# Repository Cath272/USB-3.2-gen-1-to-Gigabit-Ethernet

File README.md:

# USB 3.2 gen 1 to Gigabit Ethernet
 Gigabit Ethenet to USB C using VL162 and RTL8153

 ## VL162

  - 4:2 10Gbps USB Type-C Data Switch

  - Low power consumption with 6mW active at device mode

 ## RTL8153 

  - Integrated 10/100/1000M transceiver

  - Supports USB 3.0, 2.0, and 1.1

 ###  Built-in Voltage Regulators

- 5.0V to 3.3V LDO

- 3.3V to 1.2V Switching regulator

 ## TLV70233DBVR

 - 5V to 3.3V LDO for spi flash and leds

 ## W25Q16BVSSIG

 - 16Mbit SPI Flash  

 ## HR911130A
 - RJ45 Port with integrated magnetics 
 - 1000 Base-T Magnetics 

## PCB 
This board uses a 4 layer stackup with a  1.6mm thickness:

- POWER/SIGNAL

- GND
  
- GND
  
- POWER/SIGNAL

High Speed diferential lines need a refrence ground plane so internal planes are ground referance planes for the High speed USB lines

### Schematic:

## PCB Screenshots

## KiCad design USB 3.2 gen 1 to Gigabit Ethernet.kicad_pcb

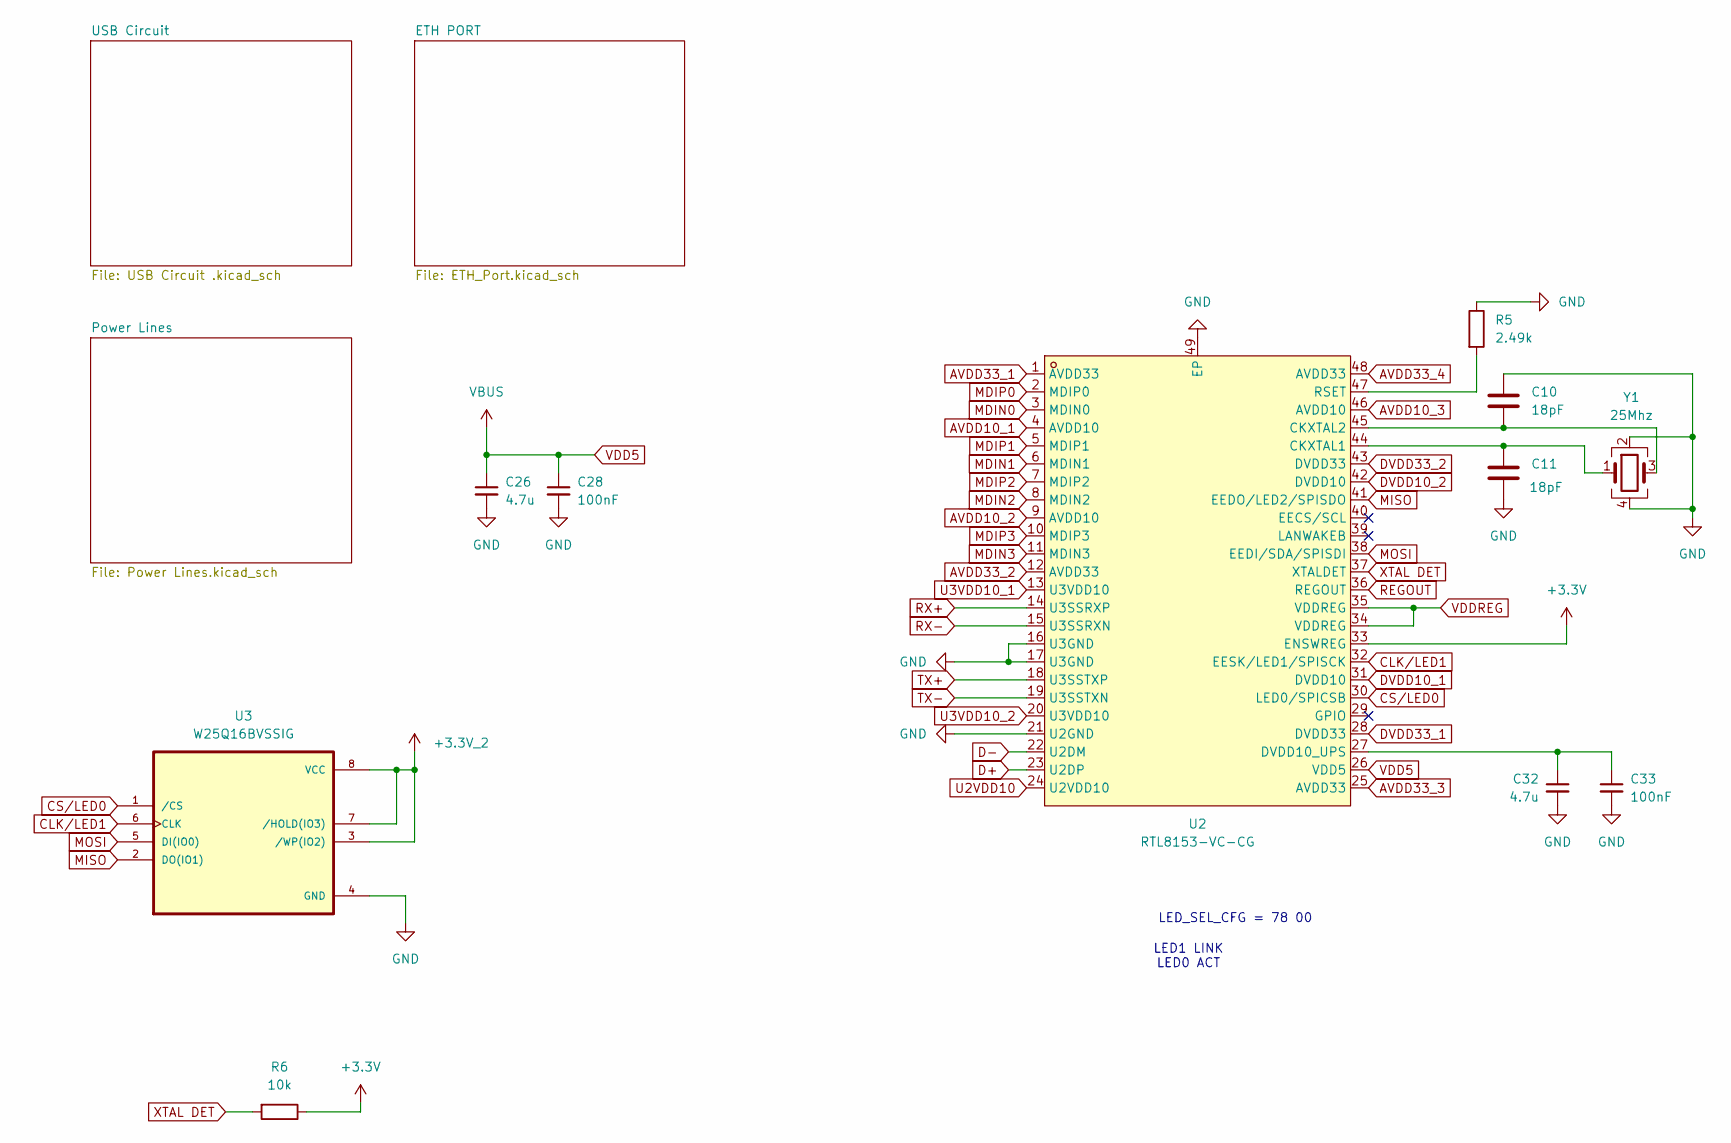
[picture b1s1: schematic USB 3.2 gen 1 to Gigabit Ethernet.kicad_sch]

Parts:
C10, C11: 18pF; C_0402_1005Metric
C26, C32: 4.7u; C_0805_2012Metric
C28, C33: 100nF; C_0402_1005Metric
R5: 2.49k; R_0402_1005Metric
R6: 10k; R_0402_1005Metric
U2: RTL8153-VC-CG; QFN-48_L6.0-W6.0-P0.40-TL-EP4.4; LCSC Part C2764167
U3: W25Q16BVSSIG; SOIC-8_L5.3-W5.3-P1.27-LS8.0-BL; PARTREV F
Y1: 25Mhz; Crystal_SMD_3225-4Pin_3.2x2.5mm

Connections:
+3.3V_2: U3.3 (/WP(IO2)), U3.7 (/HOLD(IO3)), U3.8 (VCC); also elsewhere on the board
AVDD10_1: U2.4 (AVDD10), U2.9 (AVDD10), U2.13 (U3VDD10), U2.20 (U3VDD10), U2.24 (U2VDD10), U2.31 (DVDD10), U2.42 (DVDD10), U2.46 (AVDD10); also elsewhere on the board
AVDD33_1: R6.1, U2.1 (AVDD33), U2.12 (AVDD33), U2.25 (AVDD33), U2.28 (DVDD33), U2.33 (ENSWREG), U2.34 (VDDREG), U2.35 (VDDREG), U2.43 (DVDD33), U2.48 (AVDD33); also elsewhere on the board
CLK/LED1: U2.32 (EESK/LED1/SPISCK), U3.6 (CLK); also elsewhere on the board
CS/LED0: U2.30 (LED0/SPICSB), U3.1 (/CS); also elsewhere on the board
D+: U2.23 (U2DP); also elsewhere on the board
D-: U2.22 (U2DM); also elsewhere on the board
GND: C10.1, C11.2, C26.2, C28.2, C32.2, C33.2, R5.1, U2.16 (U3GND), U2.17 (U3GND), U2.21 (U2GND), U2.49 (EP), U3.4 (GND), Y1.2, Y1.4; also elsewhere on the board
MDIN0: U2.3 (MDIN0); also elsewhere on the board
MDIN1: U2.6 (MDIN1); also elsewhere on the board
MDIN2: U2.8 (MDIN2); also elsewhere on the board
MDIN3: U2.11 (MDIN3); also elsewhere on the board
MDIP0: U2.2 (MDIP0); also elsewhere on the board
MDIP1: U2.5 (MDIP1); also elsewhere on the board
MDIP2: U2.7 (MDIP2); also elsewhere on the board
MDIP3: U2.10 (MDIP3); also elsewhere on the board
MISO: U2.41 (EEDO/LED2/SPISDO), U3.2 (DO(IO1))
MOSI: U2.38 (EEDI/SDA/SPISDI), U3.5 (DI(IO0))
unnamed: C11.1, U2.44 (CKXTAL1), Y1.1
unnamed: C10.2, U2.45 (CKXTAL2), Y1.3
unnamed: C32.1, C33.1, U2.27 (DVDD10_UPS)
unnamed: R5.2, U2.47 (RSET)
REGOUT: U2.36 (REGOUT); also elsewhere on the board
RX+: U2.14 (U3SSRXP); also elsewhere on the board
RX-: U2.15 (U3SSRXN); also elsewhere on the board
TX+: U2.18 (U3SSTXP); also elsewhere on the board
TX-: U2.19 (U3SSTXN); also elsewhere on the board
VDD5: C26.1, C28.1, U2.26 (VDD5); also elsewhere on the board
XTAL DET: R6.2, U2.37 (XTALDET)

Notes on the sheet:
LED_SEL_CFG = 78 00
LED1 LINK LED0 ACT

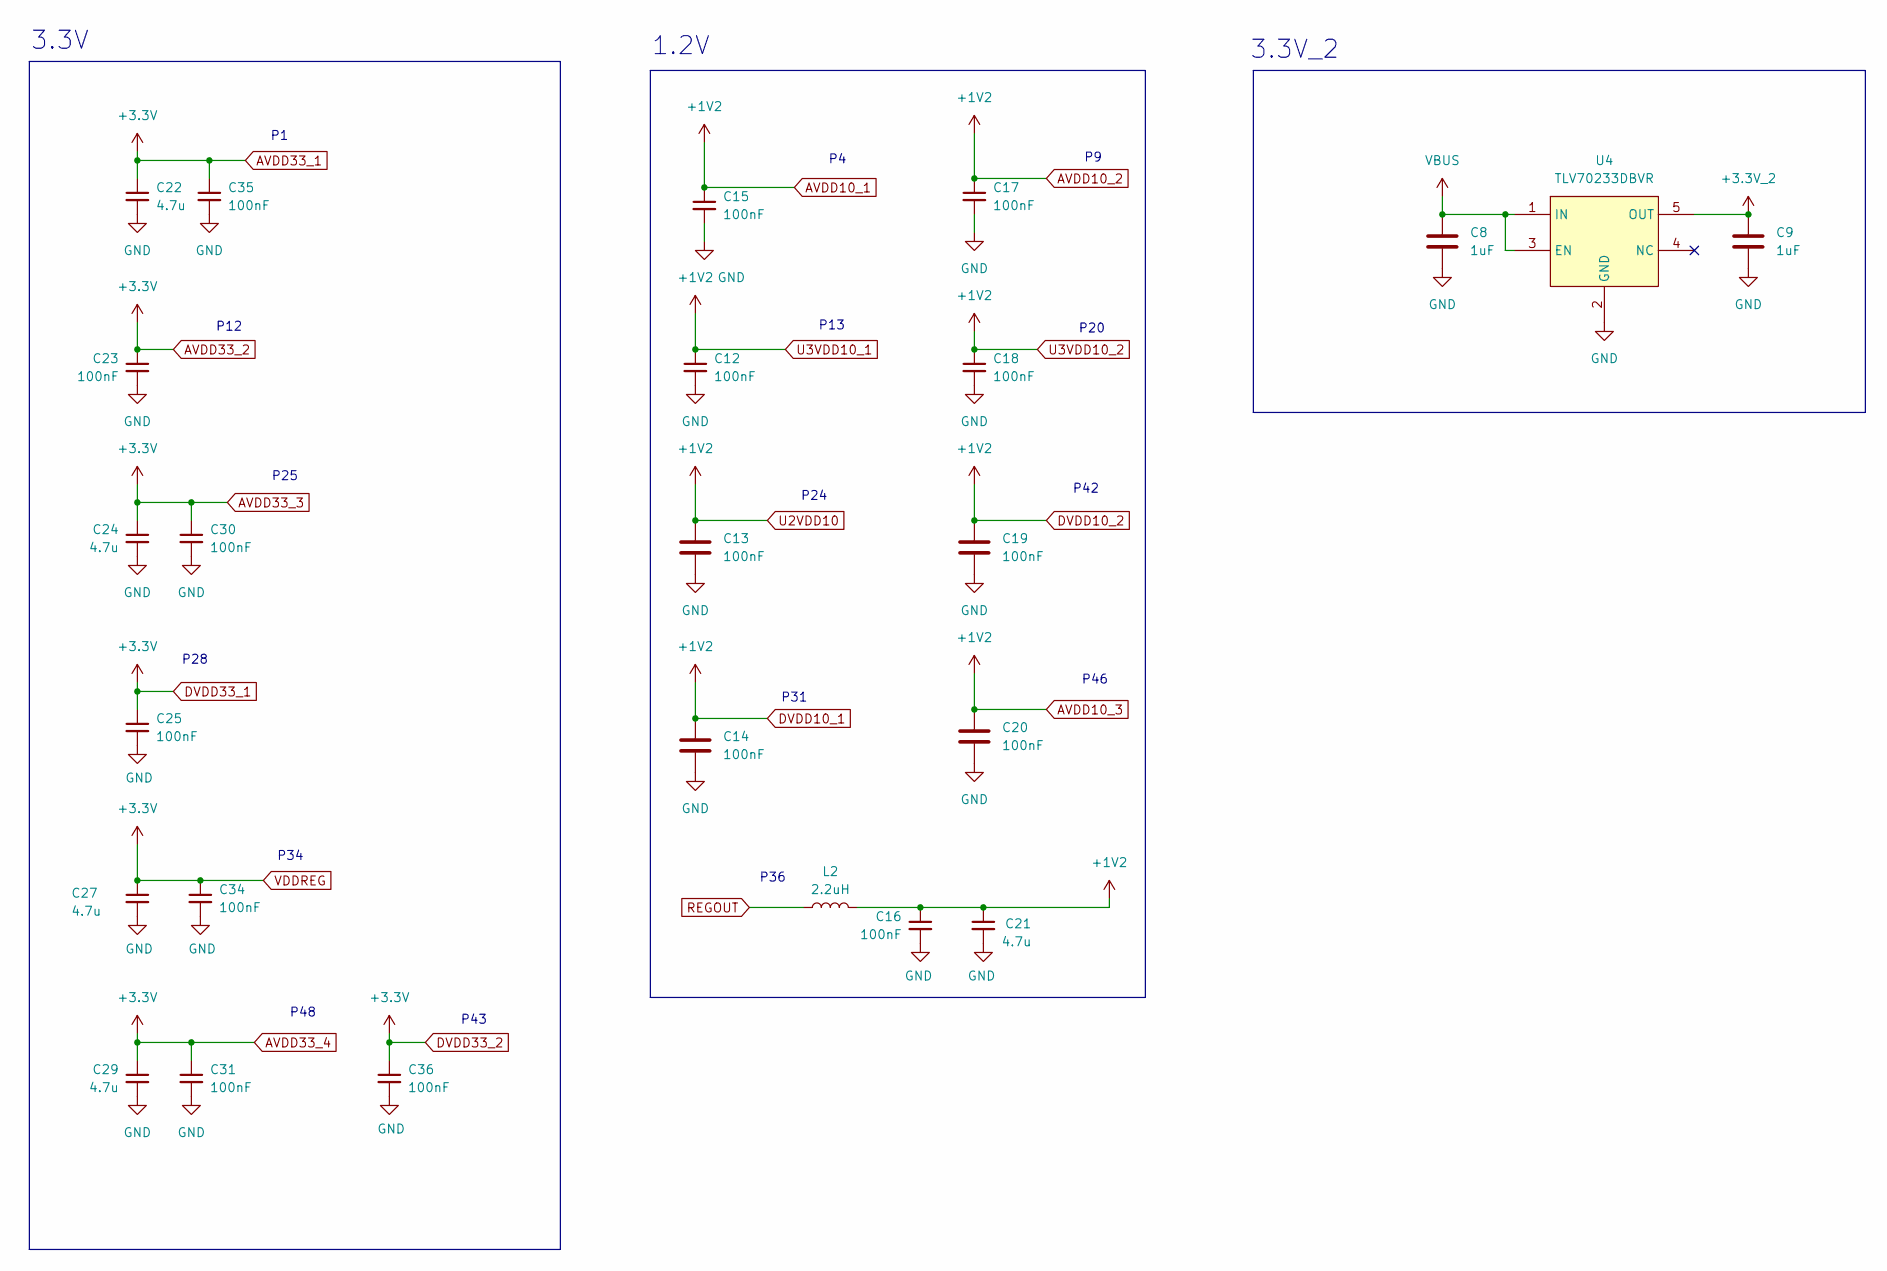
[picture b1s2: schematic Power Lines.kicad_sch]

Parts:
C8, C9: 1uF; C_0603_1608Metric
C12, C13, C14, C15, C16, C17, C18, C19, C20, C23, C25, C30, C31, C34, C35, C36: 100nF; C_0402_1005Metric
C21, C22, C24, C27, C29: 4.7u; C_0805_2012Metric
L2: 2.2uH; L_Cenker_CKCS5040
U4: TLV70233DBVR; SOT-23-5_L3.0-W1.7-P0.95-LS2.8-BR; LCSC Part C26833

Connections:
+3.3V_2: C9.1, U4.5 (OUT); also elsewhere on the board
AVDD10_1: C12.1, C13.1, C14.1, C15.1, C16.1, C17.1, C18.1, C19.1, C20.1, C21.1, L2.2; also elsewhere on the board
AVDD33_1: C22.1, C23.1, C24.1, C25.1, C27.1, C29.1, C30.1, C31.1, C34.1, C35.1, C36.1; also elsewhere on the board
GND: C8.2, C9.2, C12.2, C13.2, C14.2, C15.2, C16.2, C17.2, C18.2, C19.2, C20.2, C21.2, C22.2, C23.2, C24.2, C25.2, C27.2, C29.2, C30.2, C31.2, C34.2, C35.2, C36.2, U4.2 (GND); also elsewhere on the board
REGOUT: L2.1; also elsewhere on the board
VDD5: C8.1, U4.1 (IN), U4.3 (EN); also elsewhere on the board

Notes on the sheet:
P36
P42
P20
P28
P31
3.3V
P25
P24
P12
P13
1.2V
P48
3.3V_2
P46
P43
P34

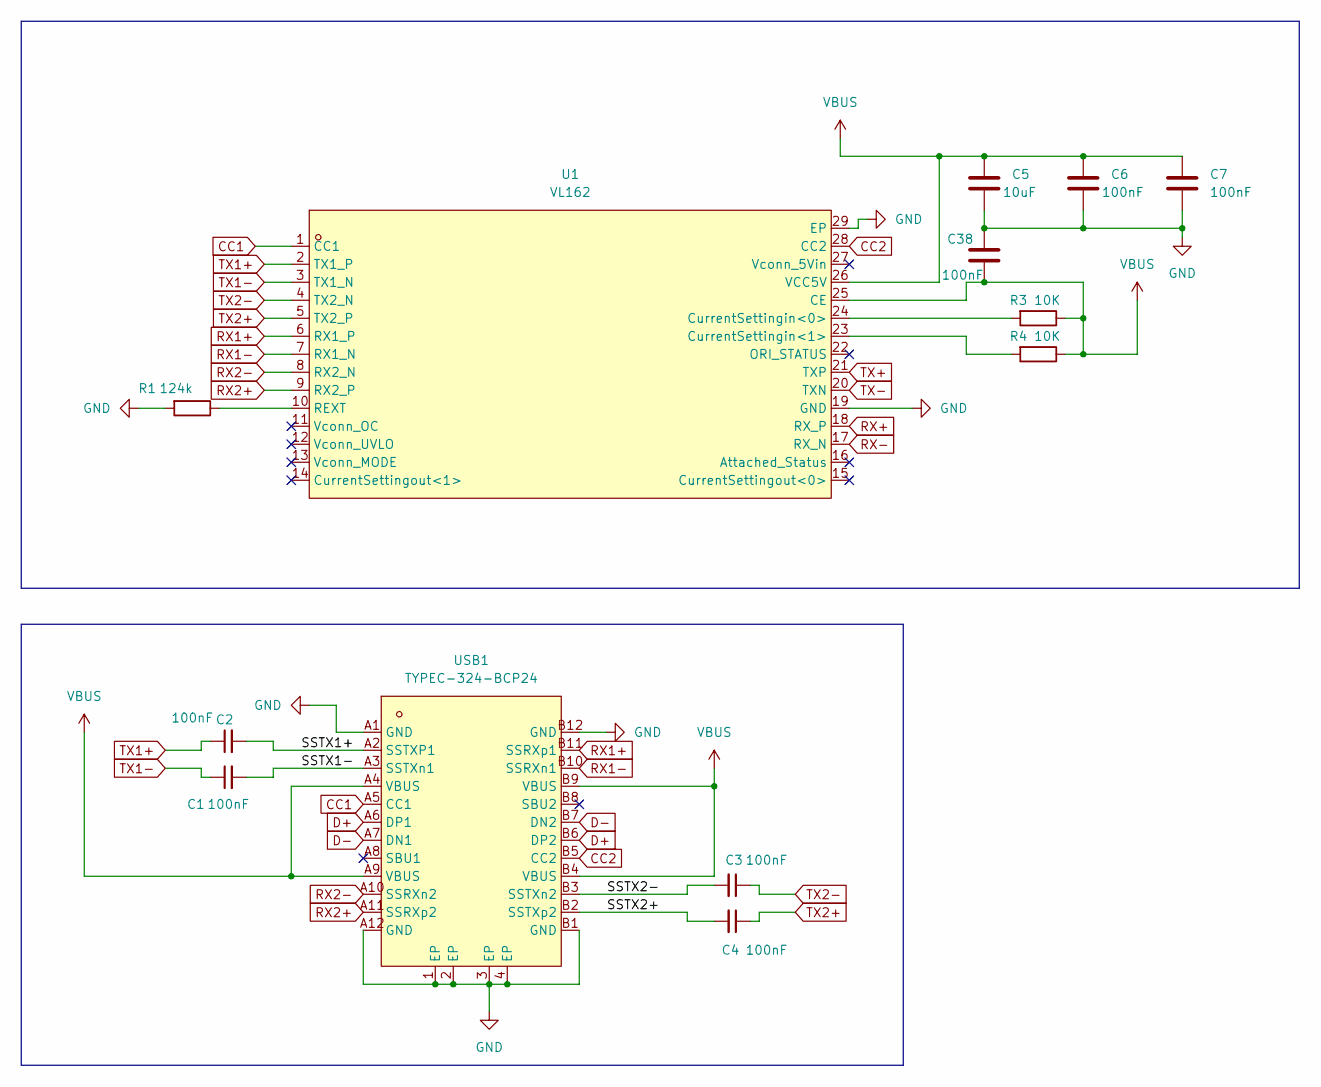
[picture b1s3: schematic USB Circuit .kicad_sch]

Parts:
C1, C2, C3, C4, C6, C7, C38: 100nF; C_0402_1005Metric
C5: 10uF; C_0805_2012Metric
R1: 124k; R_0402_1005Metric
R3, R4: 10K; R_0402_1005Metric
U1: VL162; MQFN-28_L4.5-W3.5-P0.40-BL-EP; LCSC Part C19270896
USB1: TYPEC-324-BCP24; USB-C-SMD_TYPEC-324-BCP24; LCSC Part C2835314

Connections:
/USB Circuit /SSTX1+: C2.2, USB1.A2 (SSTXP1)
/USB Circuit /SSTX1-: C1.2, USB1.A3 (SSTXn1)
/USB Circuit /SSTX2+: C4.2, USB1.B2 (SSTXp2)
/USB Circuit /SSTX2-: C3.2, USB1.B3 (SSTXn2)
CC1: U1.1 (CC1), USB1.A5 (CC1)
CC2: U1.28 (CC2), USB1.B5 (CC2)
D+: USB1.A6 (DP1), USB1.B6 (DP2); also elsewhere on the board
D-: USB1.A7 (DN1), USB1.B7 (DN2); also elsewhere on the board
GND: C5.2, C6.2, C7.2, C38.1, R1.2, U1.19 (GND), U1.29 (EP), USB1.1 (EP), USB1.2 (EP), USB1.3 (EP), USB1.4 (EP), USB1.A1 (GND), USB1.A12 (GND), USB1.B1 (GND), USB1.B12 (GND); also elsewhere on the board
unnamed: R3.2, U1.24 (CurrentSettingin<0>)
unnamed: R4.2, U1.23 (CurrentSettingin<1>)
unnamed: R1.1, U1.10 (REXT)
RX1+: U1.6 (RX1_P), USB1.B11 (SSRXp1)
RX1-: U1.7 (RX1_N), USB1.B10 (SSRXn1)
RX2+: U1.9 (RX2_P), USB1.A11 (SSRXp2)
RX2-: U1.8 (RX2_N), USB1.A10 (SSRXn2)
RX+: U1.18 (RX_P); also elsewhere on the board
RX-: U1.17 (RX_N); also elsewhere on the board
TX1+: C2.1, U1.2 (TX1_P)
TX1-: C1.1, U1.3 (TX1_N)
TX2+: C4.1, U1.5 (TX2_P)
TX2-: C3.1, U1.4 (TX2_N)
TX+: U1.21 (TXP); also elsewhere on the board
TX-: U1.20 (TXN); also elsewhere on the board
VDD5: C5.1, C6.1, C7.1, C38.2, R3.1, R4.1, U1.25 (CE), U1.26 (VCC5V), USB1.A4 (VBUS), USB1.A9 (VBUS), USB1.B4 (VBUS), USB1.B9 (VBUS); also elsewhere on the board

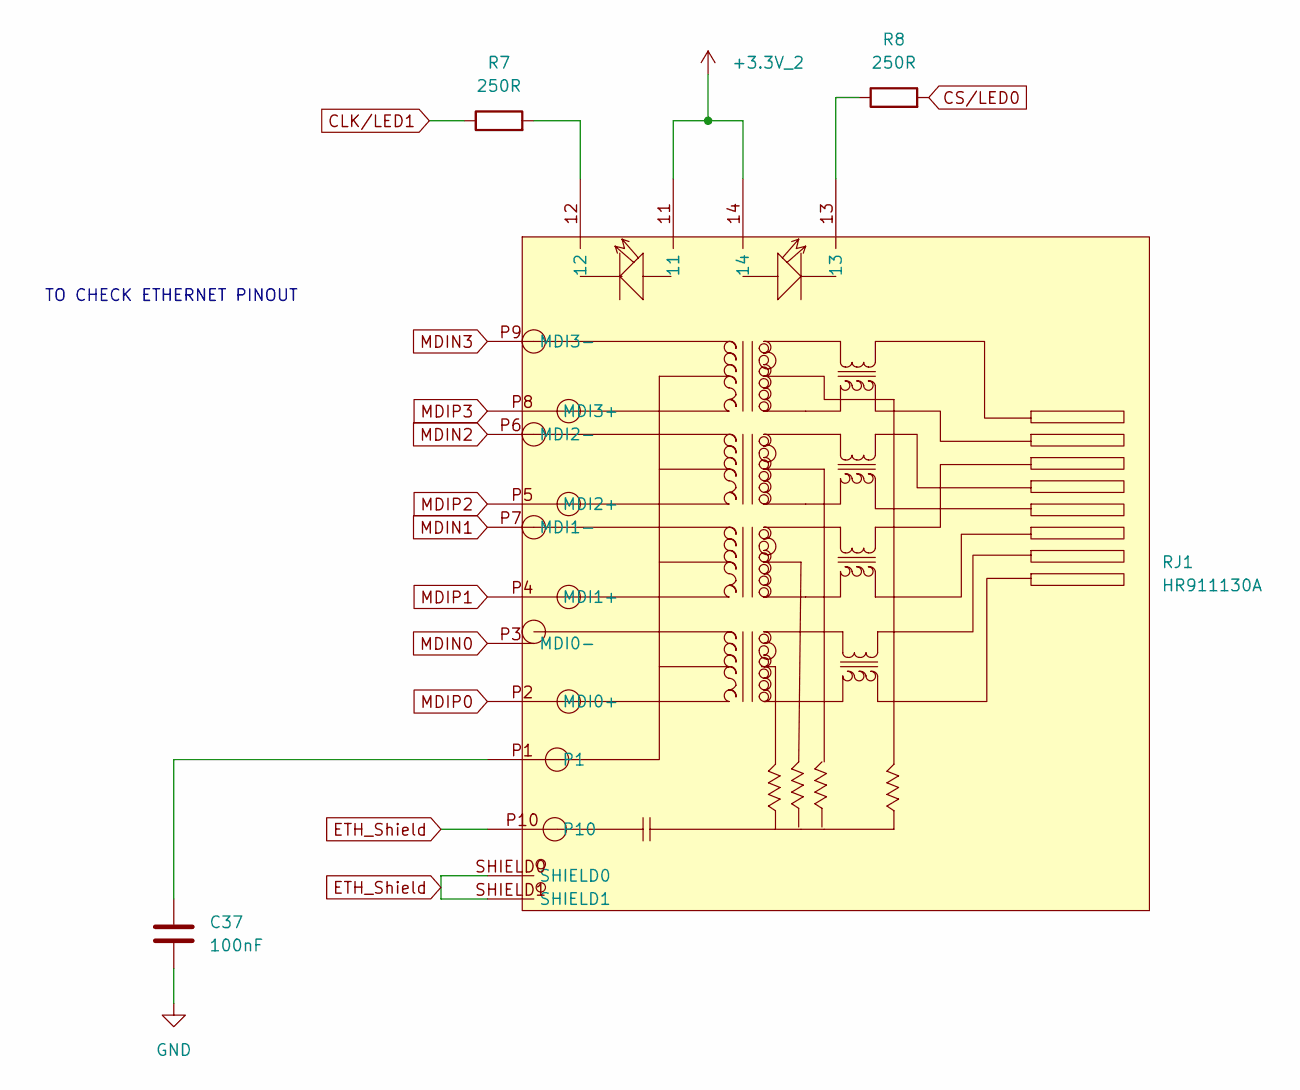
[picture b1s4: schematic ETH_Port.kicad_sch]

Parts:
C37: 100nF; C_0402_1005Metric
R7, R8: 250R; R_0402_1005Metric
RJ1: HR911130A; RJ45-TH_HR911130A; LCSC Part C54408

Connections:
+3.3V_2: RJ1.11, RJ1.14; also elsewhere on the board
CLK/LED1: R7.1; also elsewhere on the board
CS/LED0: R8.2; also elsewhere on the board
ETH_Shield: RJ1.P10, RJ1.SHIELD0, RJ1.SHIELD1
GND: C37.2; also elsewhere on the board
MDIN0: RJ1.P3 (MDI0-); also elsewhere on the board
MDIN1: RJ1.P7 (MDI1-); also elsewhere on the board
MDIN2: RJ1.P6 (MDI2-); also elsewhere on the board
MDIN3: RJ1.P9 (MDI3-); also elsewhere on the board
MDIP0: RJ1.P2 (MDI0+); also elsewhere on the board
MDIP1: RJ1.P4 (MDI1+); also elsewhere on the board
MDIP2: RJ1.P5 (MDI2+); also elsewhere on the board
MDIP3: RJ1.P8 (MDI3+); also elsewhere on the board
unnamed: C37.1, RJ1.P1
unnamed: R7.2, RJ1.12
unnamed: R8.1, RJ1.13

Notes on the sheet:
TO CHECK ETHERNET PINOUT

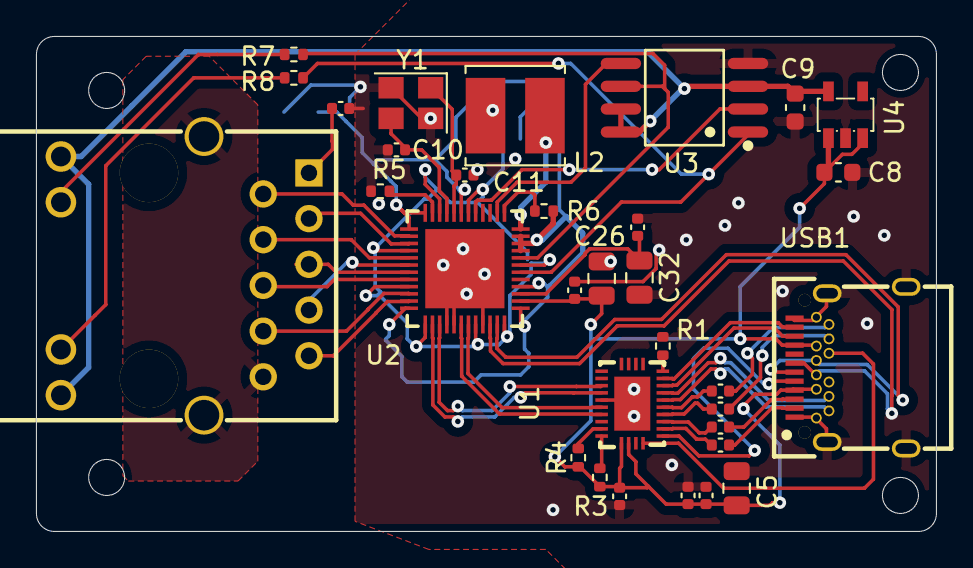
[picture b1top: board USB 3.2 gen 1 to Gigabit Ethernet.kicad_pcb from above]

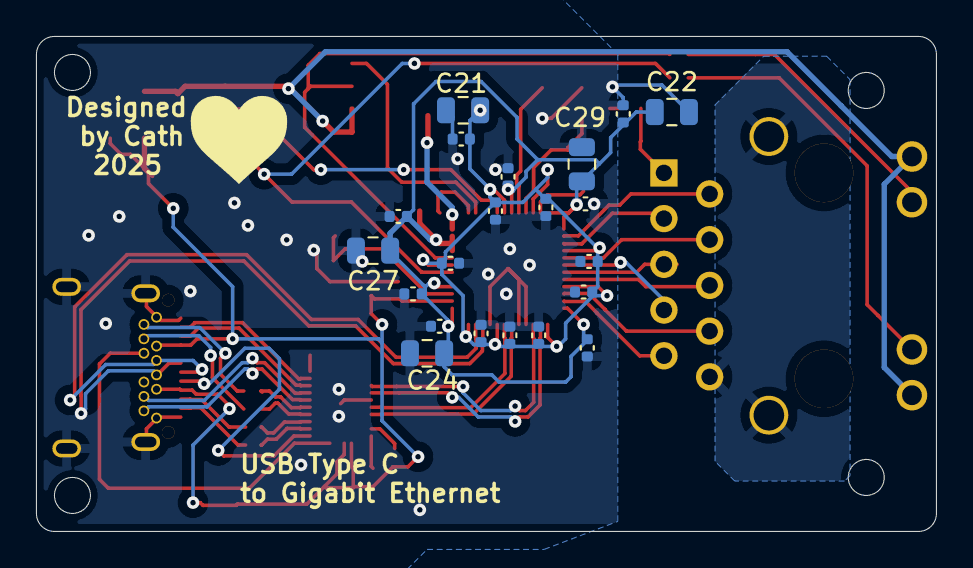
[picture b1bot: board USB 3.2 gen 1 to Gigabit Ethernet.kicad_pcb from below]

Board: 4 copper layers, 50.0 x 27.5 mm, 53 parts (21 on the bottom side), 50 nets.

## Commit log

2025-02-17 Initial release
2025-02-18 Uploaded pics
2025-02-18 Fixed readme
2025-02-18 updated gerber
2025-02-21 Fixed usb footprint
2025-03-05 fixes
